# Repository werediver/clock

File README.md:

# Clock

This [Pico](https://www.raspberrypi.com/documentation/microcontrollers/raspberry-pi-pico.html)-based clock uses a dedicated oscillator for the built-in RP2040 [RTC](https://datasheets.raspberrypi.com/rp2040/rp2040-datasheet.pdf#section_rtc), displays time using seven-segment indicators, features capacitive touch-sensing buttons, and a custom built-in NiMH charging circuit.

The estimated run-time on a single charge is _one week_ (yes, _just_ one week).

When assembling, refer to the [interactive BOM](https://htmlpreview.github.io/?https://github.com/werediver/clock/blob/main/KiCad/bom/ibom.html) page.

## NiMH battery charger

```mermaid
---
title: Charger state machine
---
stateDiagram-v2
    [*] --> Hold
    Hold --> Charge: ext_power && v < HIGH
    Charge --> Charged: d(v) ≤ NDV || is_adc_saturated() || is_timed_out()
    Charged --> Charge: v < HIGH
    Charge --> Hold: !ext_power
    Charged --> Hold: !ext_power
```

- [ ] Add a time-out for `v ≥ NiMH_HIGH` (1–2h?)

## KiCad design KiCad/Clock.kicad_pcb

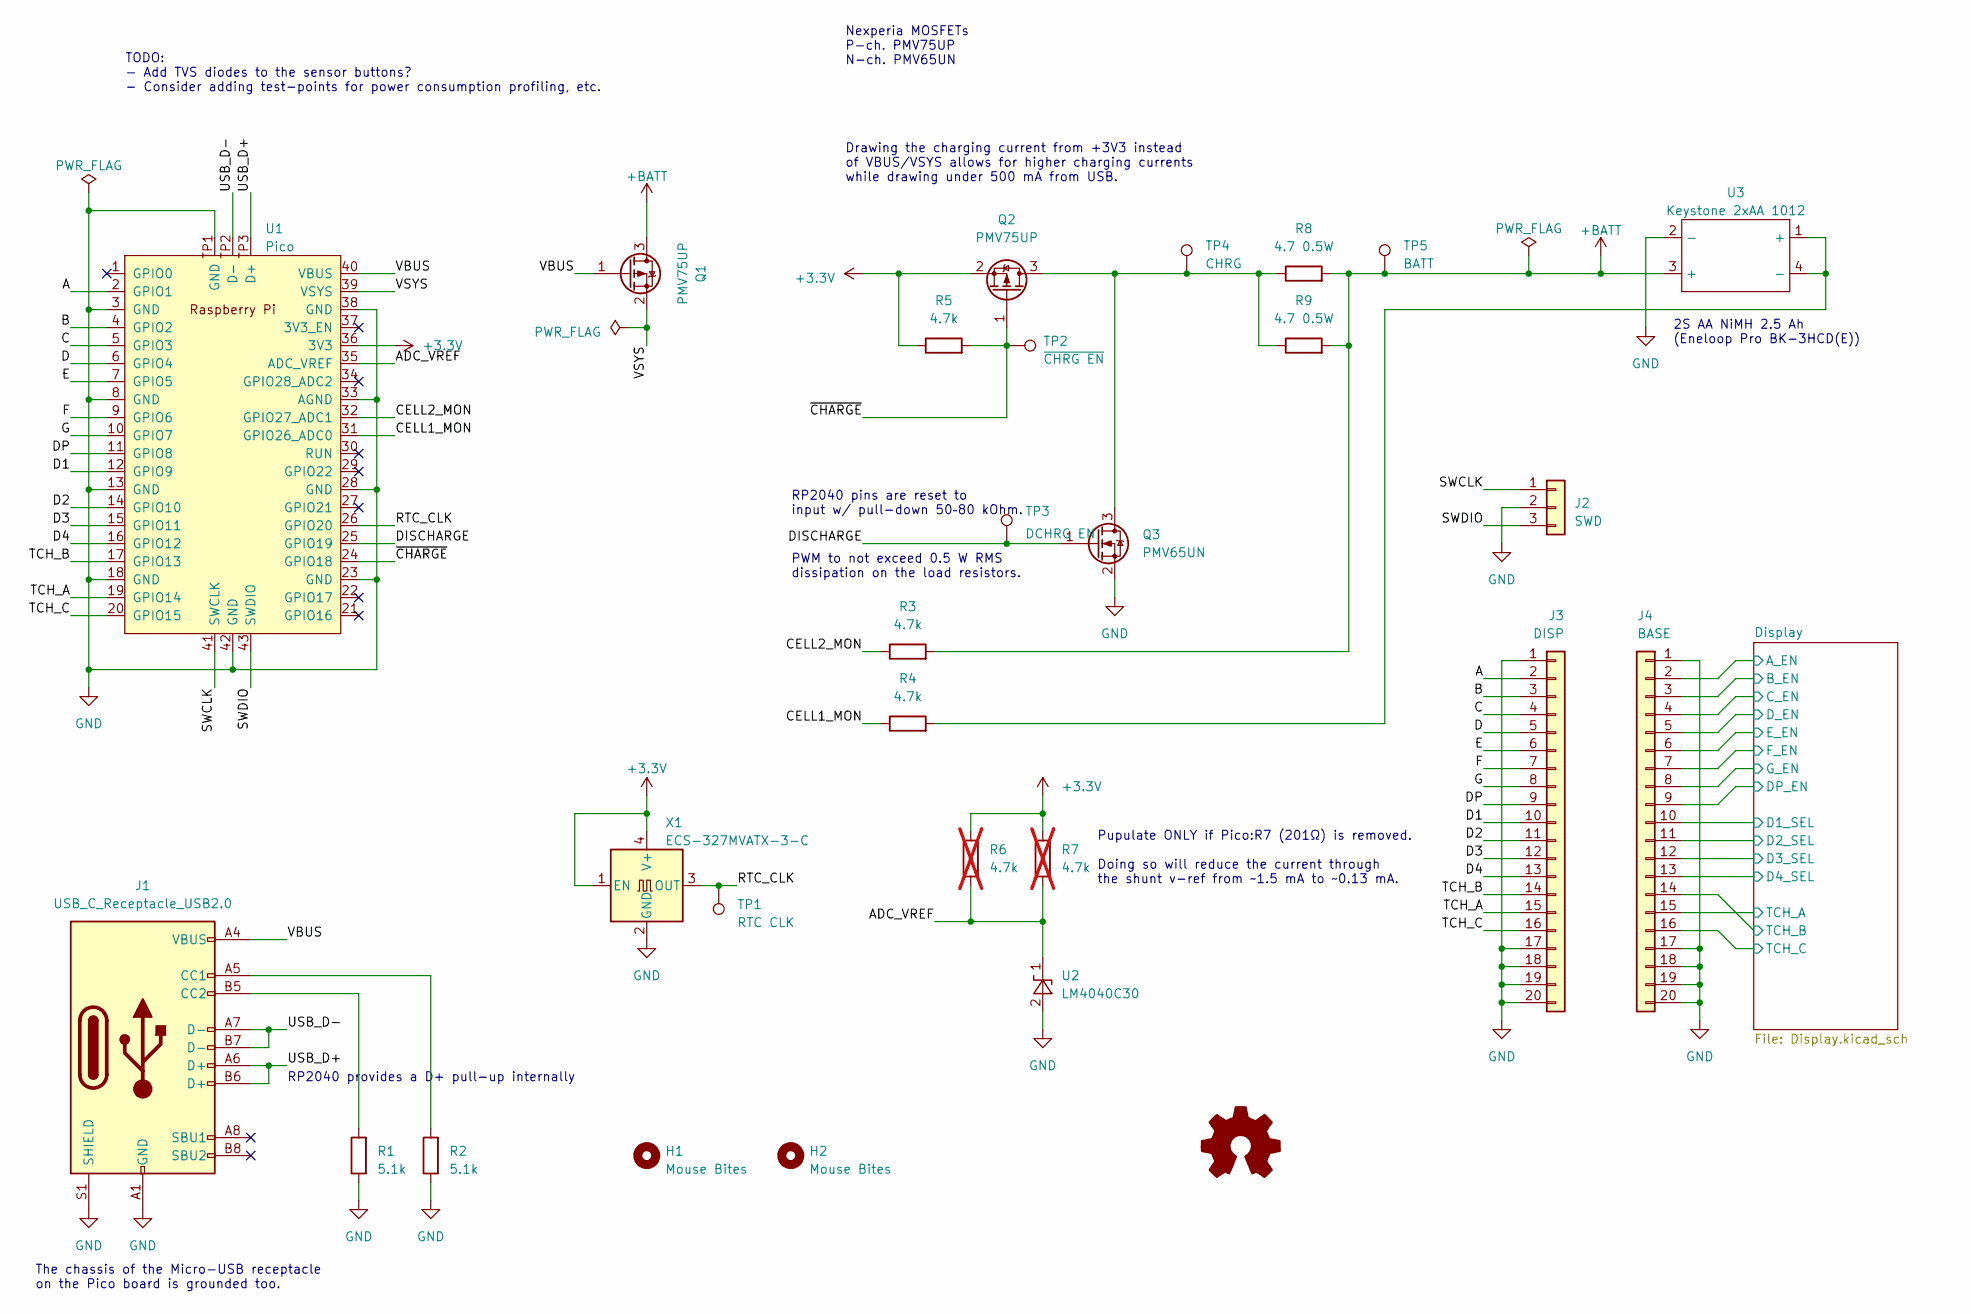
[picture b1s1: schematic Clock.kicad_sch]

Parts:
H1, H2: Mouse Bites; MouseBites_2x05mm
J1: USB_C_Receptacle_USB2.0; USB_C_Receptacle_GCT_USB4105-xx-A_16P_TopMnt_Horizontal
J2: SWD; PinHeader_1x03_P2.54mm_Horizontal
J3: DISP; PinHeader_1x20_P2.54mm_Horizontal
J4: BASE; PinSocket_1x20_P2.54mm_Vertical
Q1, Q2: PMV75UP; SOT-23
Q3: PMV65UN; SOT-23
R1, R2: 5.1k; R_1206_3216Metric_Pad1.30x1.75mm_HandSolder
R3, R4, R5: 4.7k; R_1206_3216Metric_Pad1.30x1.75mm_HandSolder
R6, R7: 4.7k; R_1206_3216Metric_Pad1.30x1.75mm_HandSolder; not fitted
R8, R9: 4.7 0.5W; R_1206_3216Metric_Pad1.30x1.75mm_HandSolder
SYM1: Logo_Open_Hardware_Small; OSHW-Logo2_24.3x20mm_SilkScreen
TP1: RTC CLK; TestPoint_Pad_D2.0mm
TP2: ~{CHRG EN}; TestPoint_Pad_D2.0mm
TP3: DCHRG EN; TestPoint_Pad_D2.0mm
TP4: CHRG; TestPoint_Pad_D2.0mm
TP5: BATT; TestPoint_Pad_D2.0mm
U1: Pico; RPi_Pico_SMD
U2: LM4040C30; SOT-23
U3: Keystone 2xAA 1012; BatteryHolder_Keystone_1012_2xAA
X1: ECS-327MVATX-3-C; Oscillator_SMD_EuroQuartz_XO32-4Pin_3.2x2.5mm_HandSoldering

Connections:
+3.3V: Q2.2 (S), R5.1, R6.2, R7.2, U1.36 (3V3), X1.1 (EN), X1.4 (V+)
+BATT: Q1.3 (D), R3.2, R8.2, R9.2, TP5.1, U3.3 (+)
/A: J3.2, U1.2 (GPIO1)
/ADC_VREF: R6.1, R7.1, U1.35 (ADC_VREF), U2.1 (K)
/B: J3.3, U1.4 (GPIO2)
/C: J3.4, U1.5 (GPIO3)
/CELL1_MON: R4.1, U1.31 (GPIO26_ADC0)
/CELL2_MON: R3.1, U1.32 (GPIO27_ADC1)
/D: J3.5, U1.6 (GPIO4)
/D1: J3.10, U1.12 (GPIO9)
/D2: J3.11, U1.14 (GPIO10)
/D3: J3.12, U1.15 (GPIO11)
/D4: J3.13, U1.16 (GPIO12)
/DISCHARGE: Q3.1 (G), TP3.1, U1.25 (GPIO19)
/DP: J3.9, U1.11 (GPIO8)
/Display/A_EN: J4.2; also elsewhere on the board
/Display/B_EN: J4.3; also elsewhere on the board
/Display/C_EN: J4.4; also elsewhere on the board
/Display/D1_SEL: J4.10; also elsewhere on the board
/Display/D2_SEL: J4.11; also elsewhere on the board
/Display/D3_SEL: J4.12; also elsewhere on the board
/Display/D4_SEL: J4.13; also elsewhere on the board
/Display/DP_EN: J4.9; also elsewhere on the board
/Display/D_EN: J4.5; also elsewhere on the board
/Display/E_EN: J4.6; also elsewhere on the board
/Display/F_EN: J4.7; also elsewhere on the board
/Display/G_EN: J4.8; also elsewhere on the board
/E: J3.6, U1.7 (GPIO5)
/F: J3.7, U1.9 (GPIO6)
/G: J3.8, U1.10 (GPIO7)
/RTC_CLK: TP1.1, U1.26 (GPIO20), X1.3 (OUT)
/SWCLK: J2.1, U1.41 (SWCLK)
/SWDIO: J2.3, U1.43 (SWDIO)
/TCH_A: J3.15, U1.19 (GPIO14)
/TCH_B: J3.14, U1.17 (GPIO13)
/TCH_C: J3.16, U1.20 (GPIO15)
/USB_D+: J1.A6 (D+), J1.B6 (D+), U1.TP3 (D+)
/USB_D-: J1.A7 (D-), J1.B7 (D-), U1.TP2 (D-)
/VBUS: J1.A4 (VBUS), J1.A9 (VBUS), J1.B4 (VBUS), J1.B9 (VBUS), Q1.1 (G), U1.40 (VBUS)
/VSYS: Q1.2 (S), U1.39 (VSYS)
/~CHARGE: Q2.1 (G), R5.2, TP2.1, U1.24 (GPIO18)
GND: J1.A1 (GND), J1.A12 (GND), J1.B1 (GND), J1.B12 (GND), J1.S1 (SHIELD), J2.2, J3.1, J3.17, J3.18, J3.19, J3.20, J4.1, J4.17, J4.18, J4.19, J4.20, Q3.2 (S), R1.1, R2.1, U1.3 (GND), U1.8 (GND), U1.13 (GND), U1.18 (GND), U1.23 (GND), U1.28 (GND), U1.33 (AGND), U1.38 (GND), U1.42 (GND), U1.TP1 (GND), U2.2 (A), U3.2 (-), X1.2 (GND); also elsewhere on the board
unnamed: J1.A5 (CC1), R2.2
unnamed: J1.B5 (CC2), R1.2
unnamed: Q2.3 (D), Q3.3 (D), R8.1, R9.1, TP4.1
unnamed: R4.2, U3.1 (+), U3.4 (-)

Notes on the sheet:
2S AA NiMH 2.5 Ah (Eneloop Pro BK-3HCD(E))
RP2040 provides a D+ pull-up internally
PWM to not exceed 0.5 W RMS dissipation on the load resistors.
RP2040 pins are reset to input w/ pull-down 50–80 kOhm.
Nexperia MOSFETs P-ch. PMV75UP N-ch. PMV65UN
Pupulate ONLY if Pico:R7 (201Ω) is removed. Doing so will reduce the current through the shunt v-ref from ~1.5 mA to ~0.13 mA.
Drawing the charging current from +3V3 instead of VBUS/VSYS allows for higher charging currents while drawing under 500 mA from USB.
TODO: - Add TVS diodes to the sensor buttons? - Consider adding test-points for power consumption profiling, etc.
The chassis of the Micro-USB receptacle on the Pico board is grounded too.

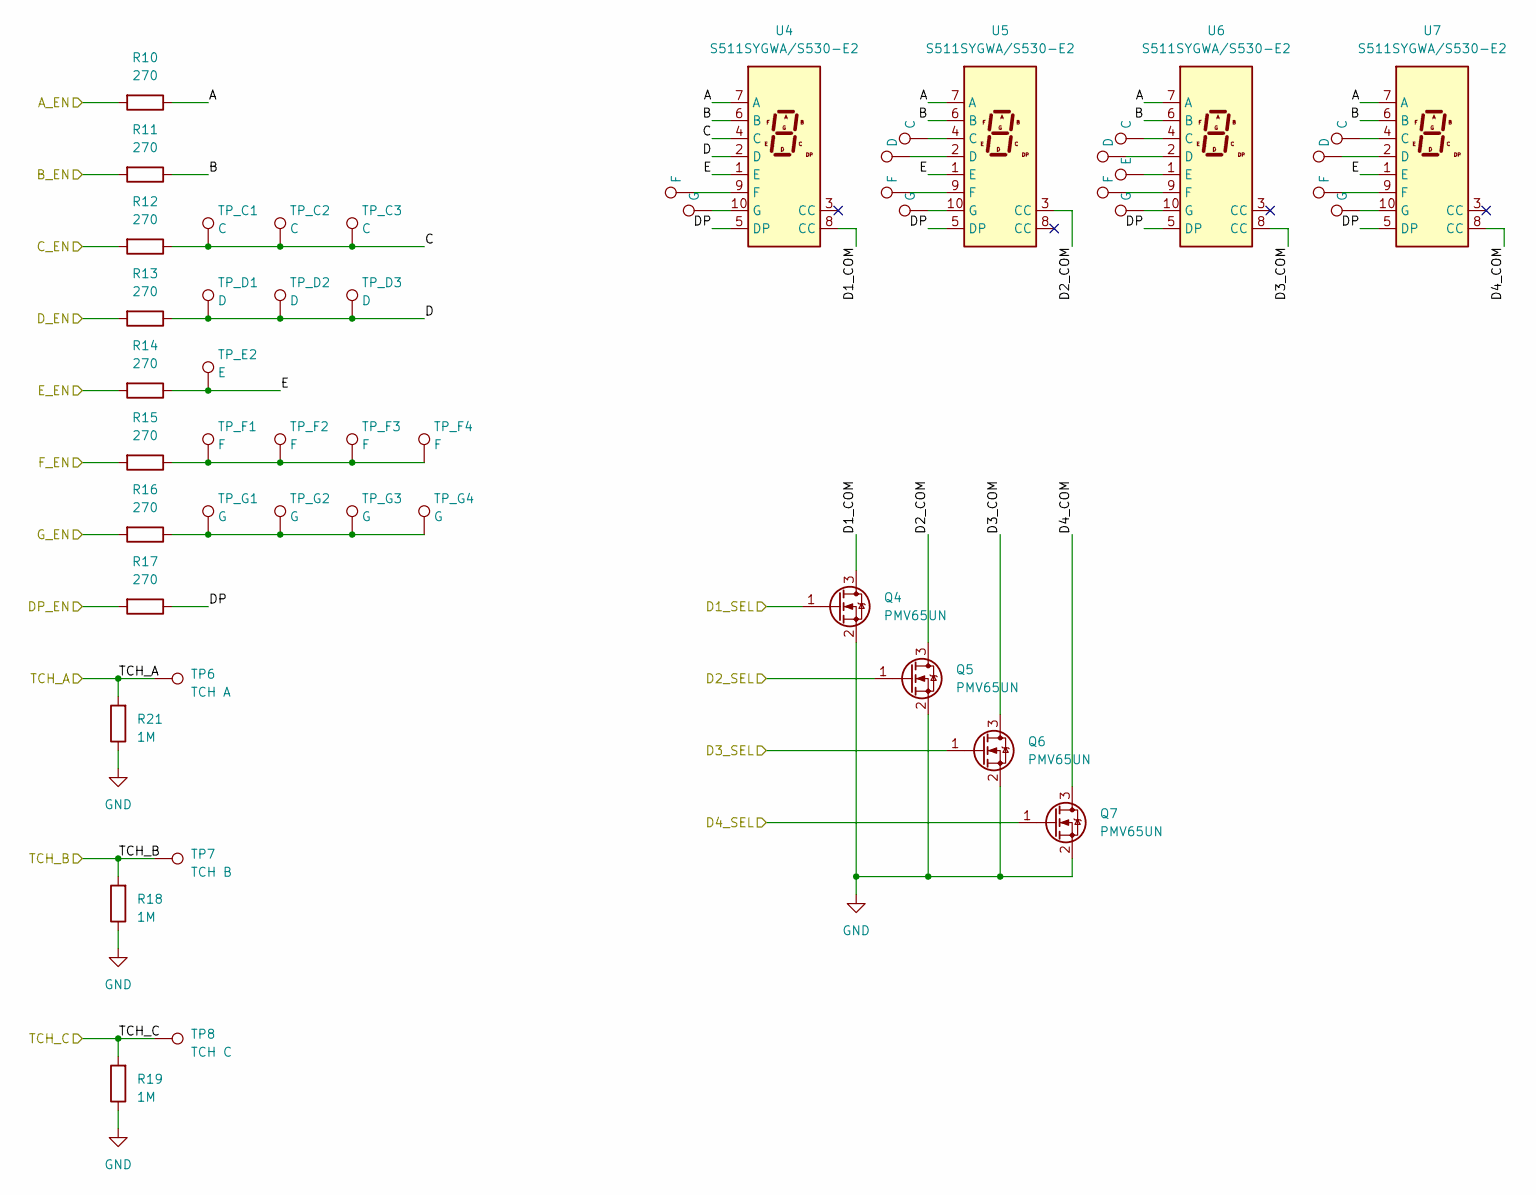
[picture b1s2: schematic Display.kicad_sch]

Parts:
Q4, Q5, Q6, Q7: PMV65UN; SOT-23
R10, R11, R12, R13, R14, R15, R16, R17: 270; R_1206_3216Metric_Pad1.30x1.75mm_HandSolder
R18, R19, R21: 1M; R_1206_3216Metric_Pad1.30x1.75mm_HandSolder
TP6: TCH A; TouchPad
TP7: TCH B; TouchPad
TP8: TCH C; TouchPad
TP_C1, TP_C2, TP_C3, TP_C6, TP_C7, TP_C8: C; TestPoint_Pad_D1.0mm
TP_D1, TP_D2, TP_D3, TP_D6, TP_D7, TP_D8: D; TestPoint_Pad_D1.0mm
TP_E2, TP_E7: E; TestPoint_Pad_D1.0mm
TP_F1, TP_F2, TP_F3, TP_F4, TP_F5, TP_F6, TP_F7, TP_F8: F; TestPoint_Pad_D1.0mm
TP_G1, TP_G2, TP_G3, TP_G4, TP_G5, TP_G6, TP_G7, TP_G8: G; TestPoint_Pad_D1.0mm
U4, U5, U6, U7: S511SYGWA/S530-E2; D1X8K

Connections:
/Display/A: R10.1, U4.7 (A), U5.7 (A), U6.7 (A), U7.7 (A)
/Display/A_EN: R10.2; also elsewhere on the board
/Display/B: R11.1, U4.6 (B), U5.6 (B), U6.6 (B), U7.6 (B)
/Display/B_EN: R11.2; also elsewhere on the board
/Display/C: R12.1, TP_C1.1, TP_C2.1, TP_C3.1, U4.4 (C)
/Display/C_EN: R12.2; also elsewhere on the board
/Display/D: R13.1, TP_D1.1, TP_D2.1, TP_D3.1, U4.2 (D)
/Display/D1_COM: Q4.3 (D), U4.8 (CC)
/Display/D1_SEL: Q4.1 (G); also elsewhere on the board
/Display/D2_COM: Q5.3 (D), U5.3 (CC)
/Display/D2_SEL: Q5.1 (G); also elsewhere on the board
/Display/D3_COM: Q6.3 (D), U6.8 (CC)
/Display/D3_SEL: Q6.1 (G); also elsewhere on the board
/Display/D4_COM: Q7.3 (D), U7.8 (CC)
/Display/D4_SEL: Q7.1 (G); also elsewhere on the board
/Display/DP: R17.1, U4.5 (DP), U5.5 (DP), U6.5 (DP), U7.5 (DP)
/Display/DP_EN: R17.2; also elsewhere on the board
/Display/D_EN: R13.2; also elsewhere on the board
/Display/E: R14.1, TP_E2.1, U4.1 (E), U5.1 (E), U7.1 (E)
/Display/E_EN: R14.2; also elsewhere on the board
/Display/F_EN: R15.2; also elsewhere on the board
/Display/G_EN: R16.2; also elsewhere on the board
GND: Q4.2 (S), Q5.2 (S), Q6.2 (S), Q7.2 (S), R18.1, R19.1; also elsewhere on the board
unnamed: R15.1, TP_F1.1, TP_F2.1, TP_F3.1, TP_F4.1
unnamed: R16.1, TP_G1.1, TP_G2.1, TP_G3.1, TP_G4.1
unnamed: TP_F5.1, U4.9 (F)
unnamed: TP_G5.1, U4.10 (G)
unnamed: TP_C6.1, U5.4 (C)
unnamed: TP_D6.1, U5.2 (D)
unnamed: TP_F6.1, U5.9 (F)
unnamed: TP_G6.1, U5.10 (G)
unnamed: TP_C7.1, U6.4 (C)
unnamed: TP_D7.1, U6.2 (D)
unnamed: TP_E7.1, U6.1 (E)
unnamed: TP_F7.1, U6.9 (F)
unnamed: TP_G7.1, U6.10 (G)
unnamed: TP_C8.1, U7.4 (C)
unnamed: TP_D8.1, U7.2 (D)
unnamed: TP_F8.1, U7.9 (F)
unnamed: TP_G8.1, U7.10 (G)

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
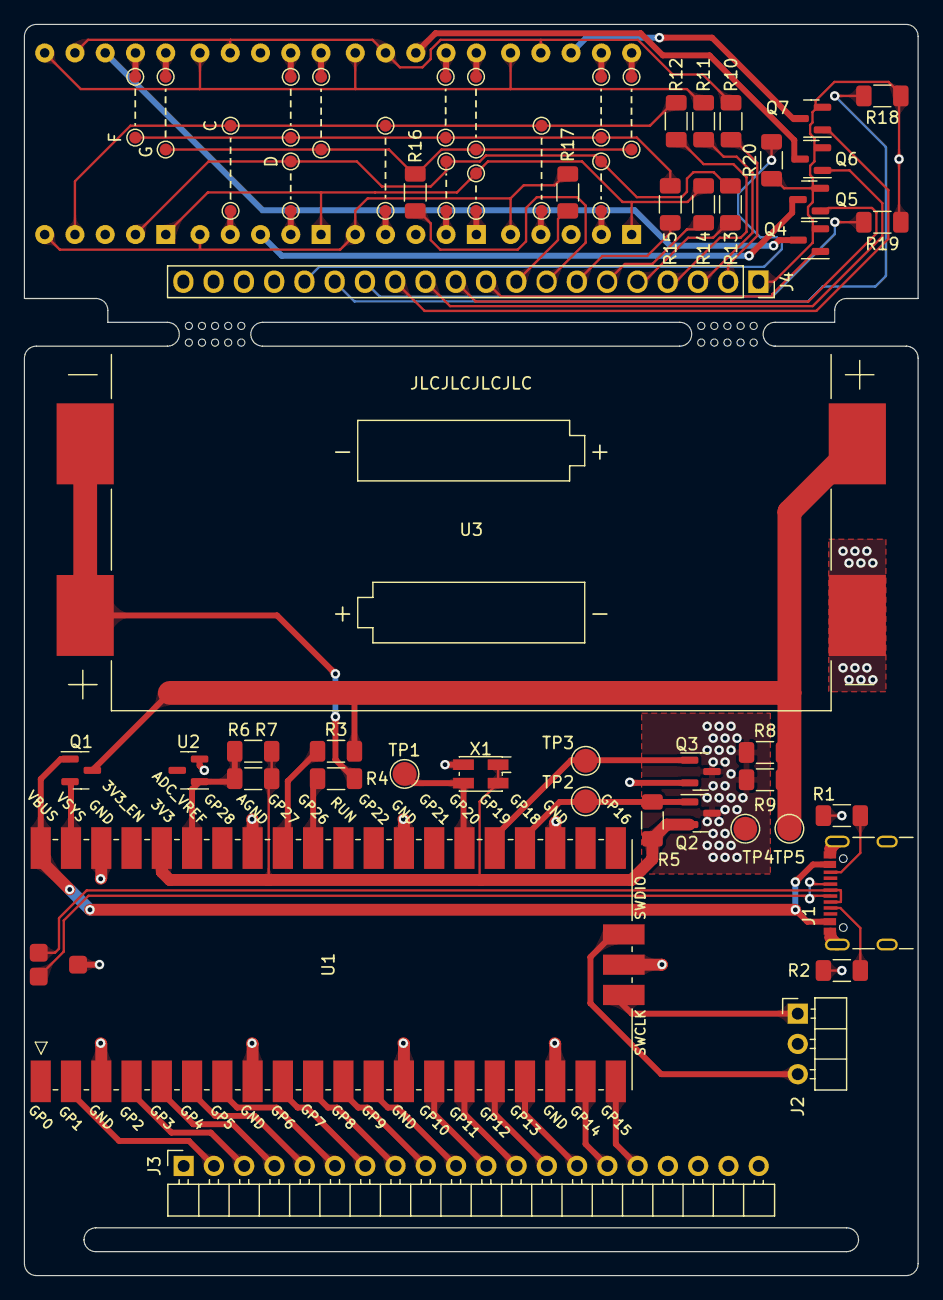
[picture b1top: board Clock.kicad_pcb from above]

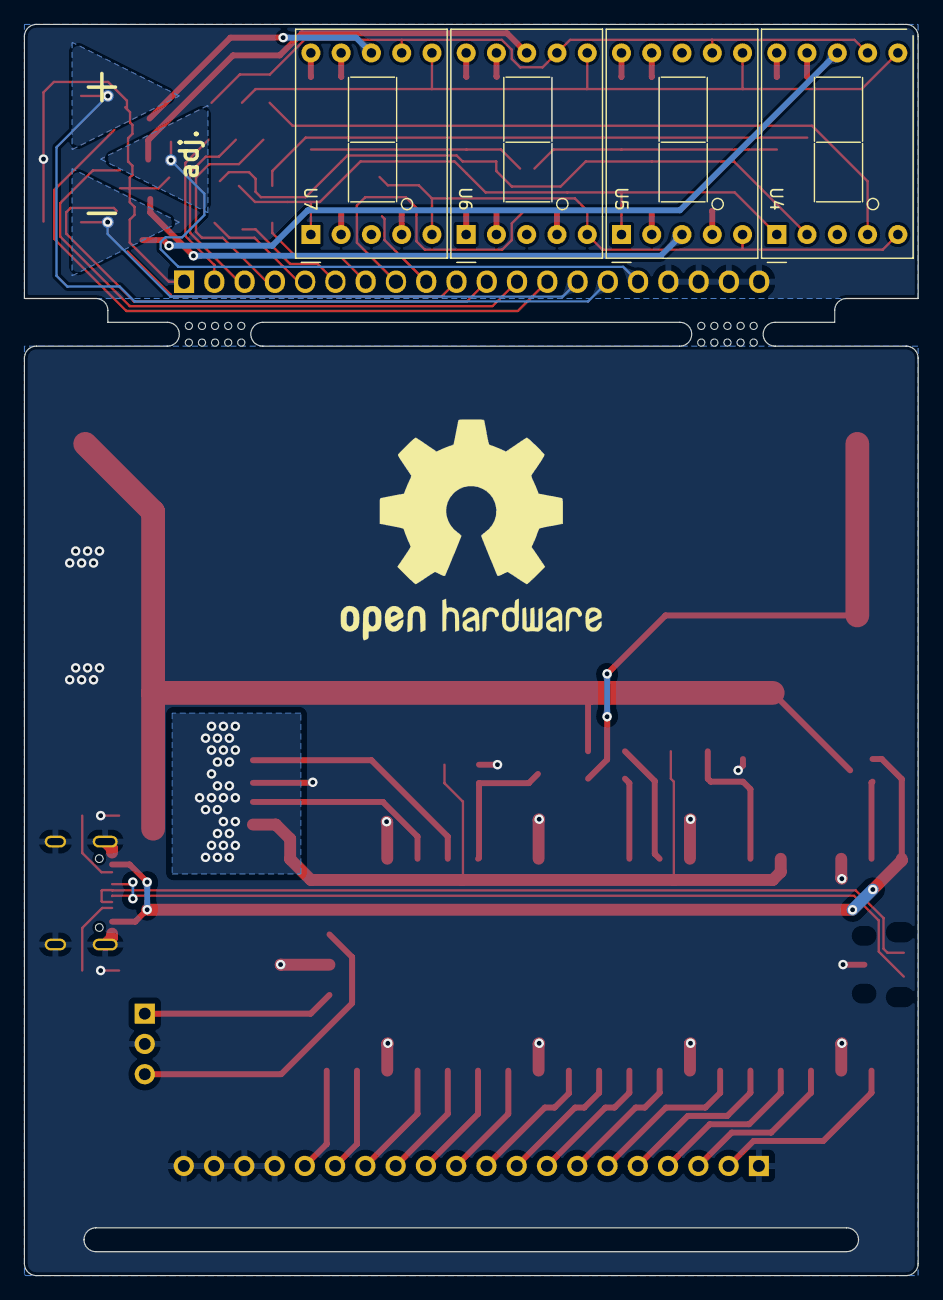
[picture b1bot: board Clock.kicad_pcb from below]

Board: 2 copper layers, 75.0 x 105.0 mm, 80 parts (8 on the bottom side), 76 nets.

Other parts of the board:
R20: 1M; R_1206_3216Metric_Pad1.30x1.75mm_HandSolder

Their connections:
GND: R20.1; also elsewhere on the board

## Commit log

2023-02-27 A completed KiCad project (may still receive minor updates)
2023-02-27 Add teardrops
2023-02-27 Update README, add 3D renders of the PCB
2023-02-27 Adjust the PCB for fabrication
2023-03-01 Make sure all Pico SM pads belong to "F.Paste" layer
2023-03-10 Attach the 3D model of Pico (again), update TODOs, update ".gitignore"
2023-03-31 Update the charge-discharge current limiting resistors from 4.7R to 5.6R (what I had in stock when assembling the boards)
2023-03-31 Add the interactive BOM files
2023-03-31 Add a photo and a link to the interactive BOM to the README
2023-03-31 Fix the link to the interactive BOM, update image alignment in README
2023-04-02 Add firmware code with a basic display driver
2023-04-05 A bit more code to work with the display (displaying decimal numbers)
2023-04-07 Initialize RTC (w/ hard-coded time), render "hh.mm"
2023-04-07 Rework "hh.mm" rendering
2023-04-09 Introduce "uptime.rs" (improved compared to the earlier versions)
2023-04-09 Make `SYST_RELOAD_COUNT` `u64` in "uptime.rs".
2023-04-09 Extend "seg-disp" to support arbitrary duty cycle (brightness control)
2023-04-30 Introduce a timed-task scheduler
2023-04-30 Add VS Code tasks to flash debug and release versions using BMP
2023-04-30 Extract the display update logic into `app_core::features::display`
2023-04-30 Extract the display h/w init & update code into a separate file
2023-06-19 Add battery charging logic
2023-09-15 Add charge indication, turn display off when depleted
